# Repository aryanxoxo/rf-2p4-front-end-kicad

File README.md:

# 2.4 GHz RF Front-End KiCad Project

> Public archive note: this repository is a portfolio/demo-safe version prepared from private working repositories/materials; sensitive details, credentials, raw logs, and proprietary context are intentionally omitted.

This is a real KiCad project scaffold for a compact 2.4 GHz RF front end, not a portfolio mockup.

## What Is Included

- `rf_2p4_front_end.kicad_pro`: KiCad project file with an RF netclass.
- `rf_2p4_front_end.kicad_pcb`: Two-layer PCB layout with board outline, edge-launch SMA pads, 50 ohm RF routes, 0402 matching parts, SOT-363 RF amplifier footprint, ground pours, and via stitching.
- `rf_2p4_front_end.kicad_sch`: Schematic intent sheet with the RF signal chain and starting component values.
- `stackup_and_tuning_notes.md`: Fabrication, impedance, and VNA tuning notes.

## Stackup Assumption

The PCB is set up for a common low-cost two-layer FR-4 stackup:

- Board thickness: 1.6 mm
- Copper: 1 oz outer
- Dielectric: FR-4, Er about 4.2
- Top RF trace width: 3.0 mm nominal for approximately 50 ohm microstrip over a solid bottom ground plane

If your board house uses a different stackup, update the RF track width before ordering.

## Important Fabrication Notes

Open the project in KiCad and run DRC before fabrication. KiCad is not installed in this Codex environment, so Gerbers were not exported or validated here.

Before ordering, replace the generic SMA edge-launch and SOT-363 amplifier footprints with the exact manufacturer land patterns for your selected connector and RF amplifier. The included geometry is suitable as an editable RF layout starting point.

## Suggested Bring-Up

1. Populate J1/J2, C1, L1, C2, C3, and U1.
2. Start with C1 = 100 pF, L1 = 3.9 nH, C2 = 1.2 pF, C3 = 100 pF.
3. Calibrate the VNA to the SMA reference plane.
4. Measure S11 and S21 from 2.3 GHz to 2.6 GHz.
5. Re-tune L1/C2 to center the match across 2.4 GHz to 2.5 GHz.

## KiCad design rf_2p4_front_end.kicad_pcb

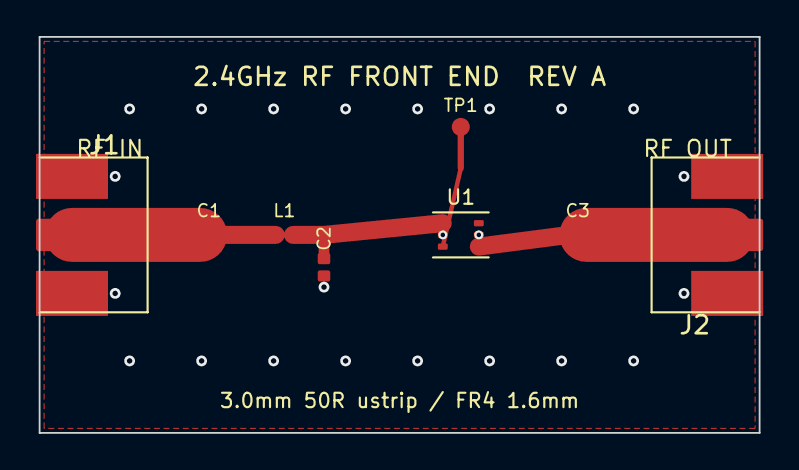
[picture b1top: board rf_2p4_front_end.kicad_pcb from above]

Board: 2 copper layers, 40.0 x 22.0 mm, 8 parts (0 on the bottom side), 7 nets.

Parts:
C1, C3: 100pF; C_0402_RF
C2: 1.2pF; C_0402_Shunt
J1: SMA_EDGE; SMA_Edge_Launch_Input
J2: SMA_EDGE; SMA_Edge_Launch_Output
L1: 3.9nH; L_0402_RF
TP1: VCC; Bias_Test_Pads
U1: RF_AMP_SOT363; SOT-363_RF_AMP

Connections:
AMP_IN: C2.1, L1.2, U1.1
AMP_OUT: C3.1, U1.4
GND: C2.2, J1.2, J1.3, J2.2, J2.3, U1.2, U1.5
MATCH_NODE: C1.2, L1.1
RF_IN: C1.1, J1.1
RF_OUT: C3.2, J2.1
VCC: TP1.1, U1.3

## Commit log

2026-06-21 Add 2.4 GHz RF front-end KiCad project
2026-06-22 Clean project documentation wording
2026-06-22 Add public archive note
